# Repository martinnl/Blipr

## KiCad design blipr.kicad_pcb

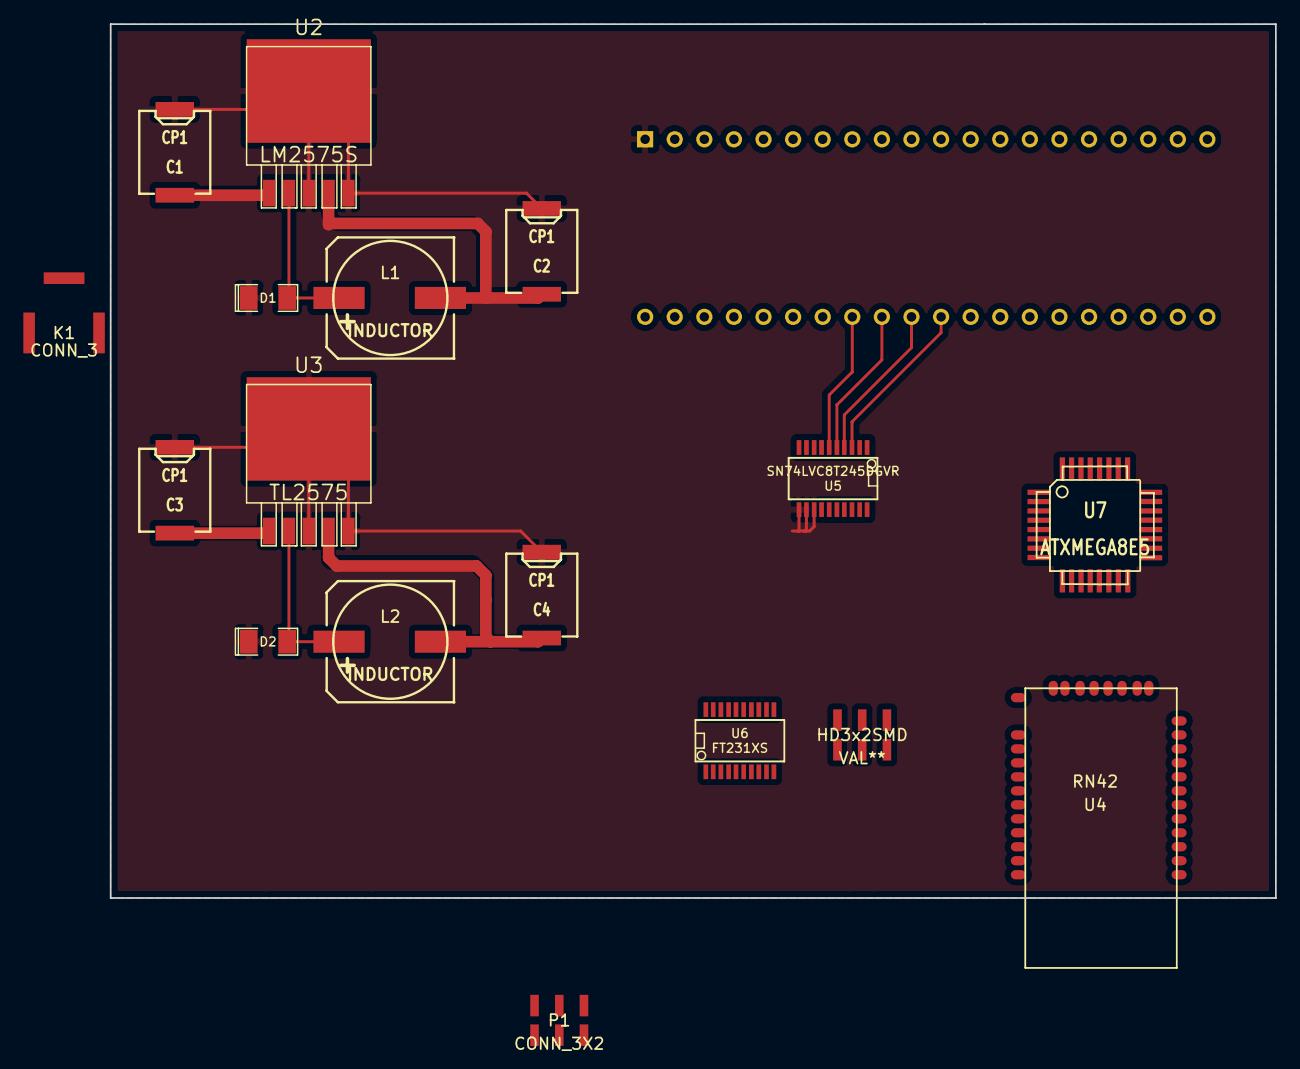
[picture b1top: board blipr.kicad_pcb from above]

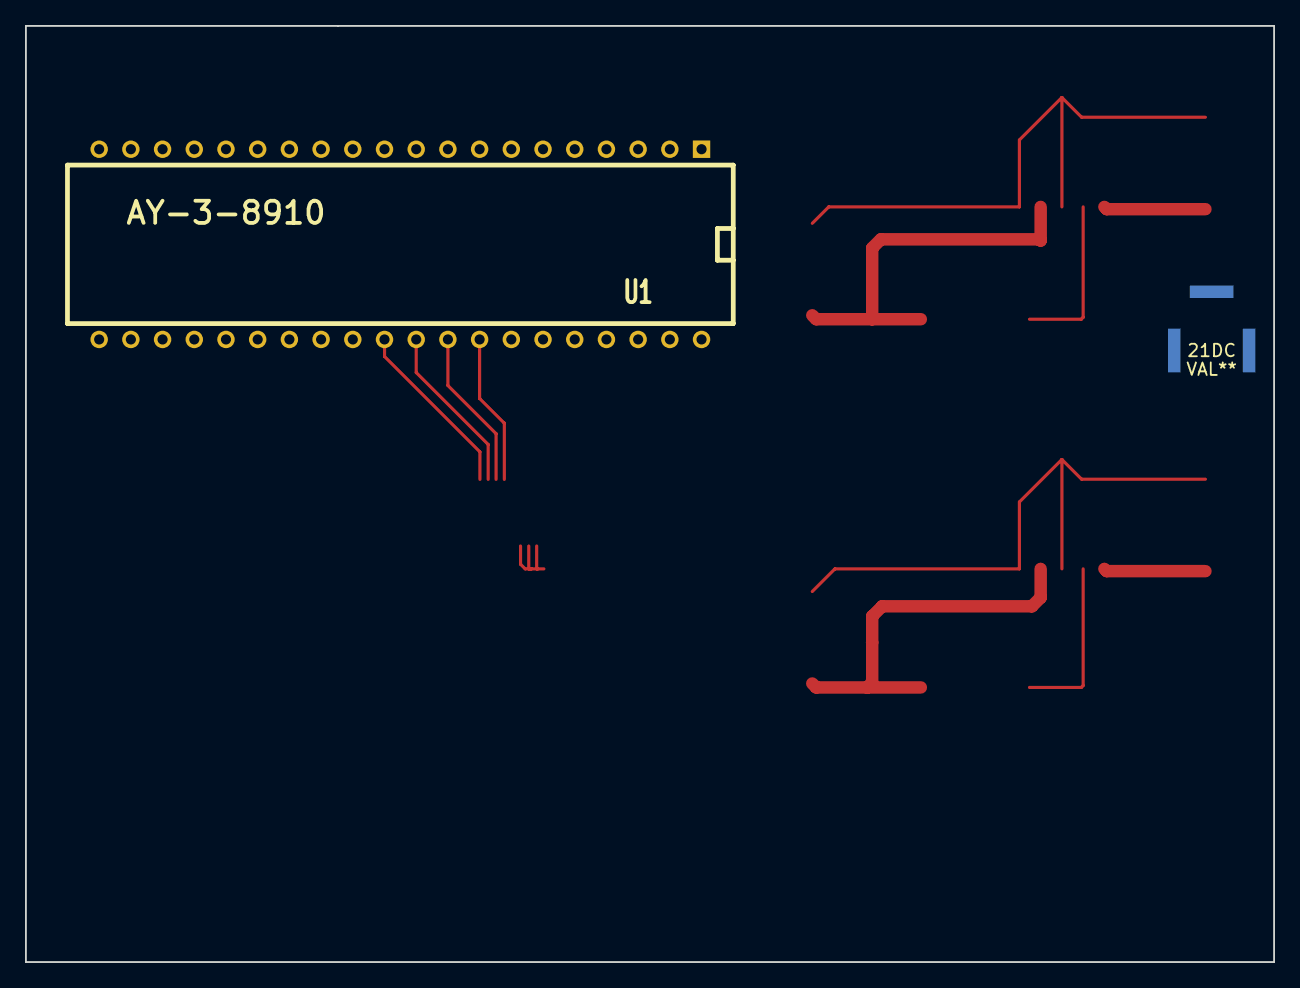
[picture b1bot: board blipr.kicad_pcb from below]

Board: 2 copper layers, 100.0 x 75.0 mm, 19 parts (2 on the bottom side), 10 nets.

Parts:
21DC: VAL**; 21DC
C1, C2, C3, C4: CP1; SMD403
D1, D2: ZENER; SM1206POL
HD3x2SMD: VAL**; HD3x2SMD
K1: CONN_3; 21DC
L1, L2: INDUCTOR; SMDSVP10
P1: CONN_3X2; HD3x2SMD
U1: AY-3-8910; DIP-40__600
U2: LM2575S; DPAK5
U3: TL2575; DPAK5
U4: RN42; RN-42
U5: SN74LVC8T245DGVR; SSOP20
U6: FT231XS; SSOP20
U7: ATXMEGA8E5; TQFP32

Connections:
+3.3V: C4.1, L2.2, U3.4
+5V: C2.1, L1.2, U2.4, U5.1
+12V: C1.1, C3.1, U2.1, U3.1
DGND: C1.2, C2.2, C3.2, C4.2, D1.1, D2.1, U1.1, U2.3, U2.5, U3.3, U3.5, U5.11, U5.12, U5.13
unnamed: U1.30, U5.3
unnamed: U1.31, U5.4
unnamed: U1.32, U5.5
unnamed: U1.33, U5.6
unnamed: D1.2, L1.1, U2.2
unnamed: D2.2, L2.1, U3.2

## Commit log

2014-03-02 Added AY-3-8910 symbol
2014-04-23 Hej
    hej
2014-04-23 Added some schematic symbols
    Added SN74LVC8T245DGVR, FT231XS, LM2575S-3.3V, TL2575HV-5V, ATXMEGA8E5
2014-04-24 Added power supply schematic and bluetooth module symbol
2014-04-25 ta bort
    skit i denna
2014-04-25 Revert "ta bort"
    This reverts commit e6ed82c02c9407b21bf66e4bbd1527b56ceedbbd.
2014-04-25 lade till en level shifter
    precis
2014-04-25 Added windows source and a test song
    precis
2014-04-25 added level shifter and bt module
2014-04-25 JAAAAAA
2014-04-25 Android app 0.1.
    I will probably need some .gitignore files for this, cleanup will follow.
2014-04-26 Added RN-42 footprint
2014-04-26 Layout 0.01
2014-04-26 Add YmReader and use it to decode the file opened.
2014-04-26 Layout 0.02
2014-04-26 Layout 0.03
2014-04-29 Added BluetoothConnection class.
